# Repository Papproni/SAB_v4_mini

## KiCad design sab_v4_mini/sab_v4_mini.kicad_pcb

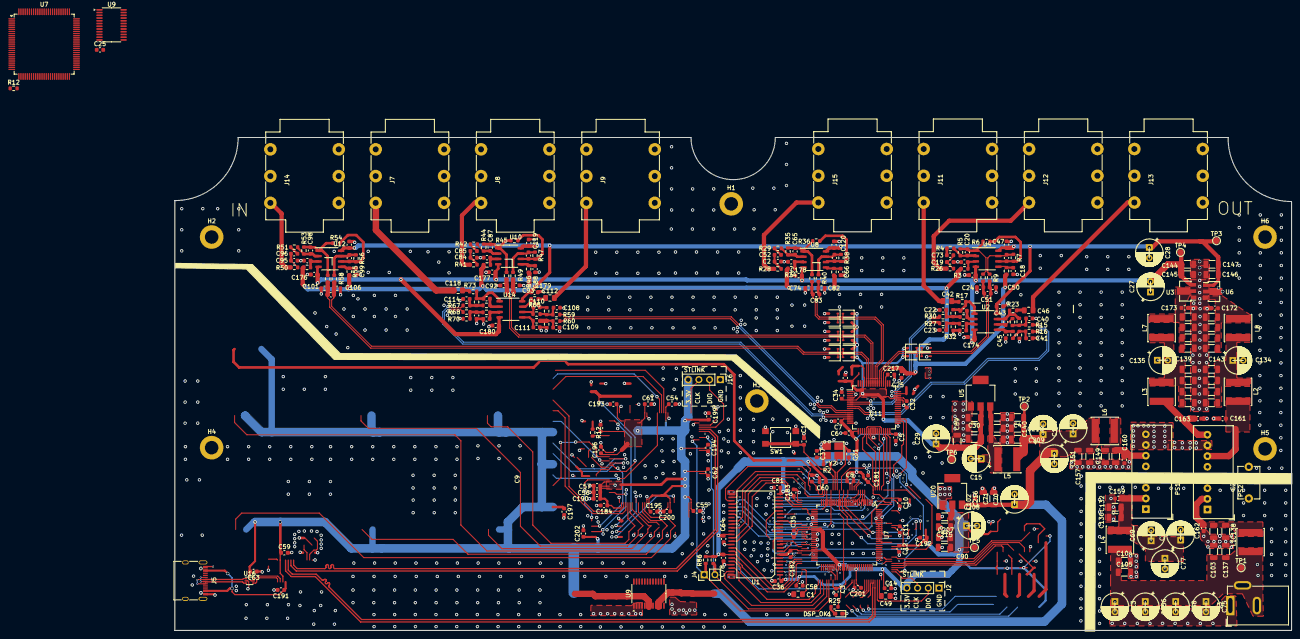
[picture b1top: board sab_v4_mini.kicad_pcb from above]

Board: 4 copper layers, 265.0 x 117.0 mm, 337 parts (0 on the bottom side), 104 nets.

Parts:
C1, C42, C46, C49, C112, C118: 2.2uF; C_0805_2012Metric_Pad1.18x1.45mm_HandSolder
C2, C19, C21, C38, C39, C44, C45, C51, C72, C83, C84, C91, C94, C95, C100, C107, C110, C111, C116, C117: 100pF; C_0603_1608Metric
C3, C5, C6, C7, C8, C9, C10, C11, C12, C14, C16, C17, C18, C25, C25#2, C32, C33, C34, C35, C36, C43, C47, C52, C53, C54, C55, C56, C57, C58, C59, C60, C61, C62, C63, C64, C66, C73, C78, C81, C85, C86, C88, C96, C97, C99, C102, C113, C119, C120, C159, C160, C161, C162, C163, C172, C173, C174, C175, C176, C177, C178, C179, C180, C181, C182, C183, C184, C190, C191, C192, C193, C194, C195, C196, C197, C198, C199, C200, C201, C202, C217: 100nF; C_0603_1608Metric
C4, C30, C71, C89, C90, C103, C104, C105, C132, C133, C136, C137, C138, C139, C141, C142, C143, C144, C145, C146, C147, C148, C149, C152, C153, C154, C155, C157, C158, C164, C165, C166, C167, C168, C169, C170, C171, C205, C206, C207, C209, C210, C211, C212, C213, C214, C215, C216: 10uF; C_1206_3216Metric
C13, C15, C27, C28, C29, C48, C69, C70, C75, C76, C77, C134, C135, C140, C150, C151, C156, C208: 100uF; CP_Radial_D6.3mm_P2.50mm_reference_fix
C20, C65, C87, C98: 1p; C_0603_1608Metric
C22, C23, C40, C41, C108, C109, C114, C115: 470pF; C_0603_1608Metric
C24, C50, C74, C82, C92, C93, C101, C106: 1nF; C_0603_1608Metric
C31, C37: 12pF; C_0603_1608Metric
C229: 1nF; C_Disc_D7.5mm_W5.0mm_P7.50mm
D1, D4, D5, D6, D7, D8, D9, D12, D13, D14, D15, D16, D17, D18, D19, D20: 1N5819; D_SOD-323
DSP_OK1: LED; LED_0603_1608Metric_Pad1.05x0.95mm_HandSolder
H1, H2, H3, H4, H5, H6: MountingHole_Pad; MountingHole_3.2mm_M3_DIN965_Pad
J2: STlink_DSP; PinHeader_1x04_P2.54mm_Vertical
J3: Barrel_Jack_Switch; BarrelJack_GCT_DCJ200-10-A_Horizontal
J4: Conn_01x02_i2c; PinHeader_1x02_P2.54mm_Vertical
J5: USB_C_Receptacle_USB2.0; USB_C_Receptacle_XKB_U262-16XN-4BVC11
J7: AudioJack_LOOP1_SEND; 6.3_jack_new_ref
J8: AudioJack_LOOP1_RETURN; 6.3_jack_new_ref
J9: AudioJack_LOOP2_SEND; 6.3_jack_new_ref
J11: AudioJack_LOOP3_SEND; 6.3_jack_new_ref
J12: AudioJack_LOOP3_RETURN; 6.3_jack_new_ref
J13: AudioJack_OUTPUT; 6.3_jack_new_ref
J14: AudioJack_INPUT; 6.3_jack_new_ref
J15: AudioJack_LOOP2_RETURN; 6.3_jack_new_ref
J16: STlink_DISP_MCU; PinHeader_1x04_P2.54mm_Vertical
L1, L2, L3, L4, L5, L6, L7, L8: 10uH; L_Sunlord_SWPA6020S
PS1: URB2405S-6WR3; Converter_DCDC_XP_POWER-ITxxxxxS_THT
PS2: WRA2412S-3WR2; Converter_DCDC_XP_POWER-ITxxxxxS_THT
R2, R3, R8, R9, R11, R26, R28, R34, R37, R39, R40, R41, R43, R46, R48, R49, R50, R52, R55, R57, R58: 100R; R_0603_1608Metric
R4, R29, R42, R51: 1M; R_0603_1608Metric
R5, R35, R44, R53: 510k; R_0603_1608Metric
R6, R7, R36, R38, R45, R47, R54, R56: 4k7; R_0603_1608Metric
R12, R12#2: 10k; R_0603_1608Metric
R13, R14, R15, R16, R19, R20, R21, R22, R27, R30, R31, R32, R59, R60, R61, R62, R63, R64, R66, R67, R68, R69, R70, R71, R72, R86: 3k; R_0603_1608Metric
R17, R23, R25, R65, R73: 1k; R_0603_1608Metric
SW1: SW_SPST; SW_SPST_TL3305A
TP1: TestPoint_PWR_IN; TestPoint_Pad_D1.5mm
TP2: TestPoint_5V; TestPoint_Pad_D1.5mm
TP3: TestPoint_9V; TestPoint_Pad_D1.5mm
TP4: TestPoint_-9V; TestPoint_Pad_D1.5mm
TP5: TestPoint_3V3; TestPoint_Pad_D1.5mm
TP6: TestPoint_3V3A; TestPoint_Pad_D1.5mm
U1: IS42S16100H-7TL; TSOP-2-50-new
U2, U4, U8, U10, U12, U14: OP275; SSOP-8_3.9x5.05mm_P1.27mm
U3: 7909; SOT-89-3
U5, U20: AP1117-33; SOT-223
U6: 7809; SOT-89-3
U7, U7#2: STM32H750VBTx; LQFP-100_14x14mm_P0.5mm
U9, U9#2: CS4270; TSSOP-24_4.4x7.8mm_P0.65mm
U11: LQFP-64_10x10mm_P0.5mm
U16: USBLC6-2P6; SOT-666
Y2: X1E0000210132; Crystal_SMD_SeikoEpson_TSX3225-4Pin_3.2x2.5mm_HandSoldering

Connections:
5V: C4.1, C70.1, C71.1, C102.1, C140.1, C148.1, C150.1, C151.1, C157.1, C209.1, C210.1, C216.1, L5.1, L6.2, TP2.1, U20.3 (VI)
+3.3V: C3.1, C5.1, C6.1, C7.1, C8.1, C9.1, C10.1, C11.1, C12.1, C14.1, C35.1, C36.1, C54.1, C55.1, C56.1, C57.1, C58.1, C59.1, C60.1, C61.1, C62.1, C63.1, C64.1, C78.1, C81.1, C90.1, C181.1, C182.1, C183.1, C184.1, C190.1, C192.1, C193.1, C194.1, C195.1, C196.1, C197.1, C198.1, C199.1, C200.1, C201.1, C202.1, C207.1, C208.1, C214.1, C215.1, J2.4, J16.4, R66.1, R86.1, TP5.1, U1.1 (VDD), U1.7 (VDDQ), U1.13 (VDDQ), U1.25 (VDD), U1.38 (VDDQ), U1.44 (VDDQ), U7.6 (VBAT), U7.11 (VDD), U7.20 (VREF+), U7.21 (VDDA), U7.27 (VDD), U7.50 (VDD), U7.75 (VDD), U7.100 (VDD), U7#2.6 (VBAT), U7#2.11 (VDD), U7#2.20 (VREF+), U7#2.21 (VDDA), U7#2.27 (VDD), U7#2.50 (VDD), U7#2.75 (VDD), U7#2.100 (VDD), U11.17 (DVDD), U11.32 (DVDD), U16.5 (VBUS), U20.2 (VO)
+3.3VA: C29.1, C30.1, C32.1, C33.1, C34.1, C89.1, C205.1, C206.1, C217.1, D4.1 (K), D5.1 (K), D7.1 (K), D9.1 (K), D13.1 (K), D15.1 (K), D17.1 (K), D19.1 (K), TP6.1, U5.2 (VO), U11.5 (AVDD), U11.45 (AVDD), U11.51 (AVDD), U11.62 (AVDD)
+9V: C28.1, C43.1, C47.1, C113.1, C119.1, C120.1, C146.1, C147.1, C179.1, TP3.1, U2.8 (V+), U4.8 (V+), U6.1 (OUT), U8.8 (V+), U10.8 (V+), U12.8 (V+), U14.8 (V+)
-9V: C27.2, C144.1, C145.1, C174.2, C175.2, C176.2, C177.2, C178.2, C180.2, TP4.1, U2.4 (V-), U3.3 (VO), U4.4 (V-), U8.4 (V-), U10.4 (V-), U12.4 (V-), U14.4 (V-)
/MCU/USB_Conn_D+: J5.A6 (D+), J5.B6 (D+), U16.1 (I/O1)
/MCU/USB_Conn_D-: J5.A7 (D-), J5.B7 (D-), U16.3 (I/O2)
/Power/+12V: C161.1, L2.1, PS2.6 (+Vout)
/Power/-12V: C163.1, L3.1, PS2.8 (-Vout)
ADC1N: C24.2, C51.2, D5.2 (A), D6.1 (K), R8.1
ADC1P: C50.1, C51.1, D1.1 (K), D4.2 (A), R9.1
ADC2N: C74.2, C83.2, D7.2 (A), D8.1 (K), R39.1
ADC2P: C82.1, C83.1, D9.2 (A), D12.1 (K), R40.1
ADC3N: C92.2, C94.2, D17.2 (A), D18.1 (K), R48.1
ADC3P: C93.1, C94.1, D19.2 (A), D20.1 (K), R49.1
ADC4N: C101.2, C107.2, D13.2 (A), D14.1 (K), R57.1
ADC4P: C106.1, C107.1, D15.2 (A), D16.1 (K), R58.1
Audio_Loop1_Return: J8.T, R41.1
Audio_Loop1_Send: C118.2, J7.T
Audio_Loop2_Return: J15.T, R28.1
Audio_Loop2_Send: C112.2, J9.T
Audio_Loop3_Return: C1.2, C2.1, C3.2, C4.2, C5.2, C6.2, C7.2, C8.2, C9.2, C10.2, C11.2, C12.2, C14.2, C15.2, C16.2, C17.2, C18.2, C19.1, C22.1, C23.2, C24.1, C27.1, C28.2, C29.2, C30.2, C31.1, C32.2, C33.2, C34.2, C35.2, C36.2, C37.1, C38.1, C40.1, C41.2, C43.2, C45.1, C47.2, C49.2, C50.2, C53.2, C54.2, C55.2, C56.2, C57.2, C58.2, C59.2, C60.2, C61.2, C62.2, C63.2, C64.2, C66.2, C70.2, C71.2, C74.1, C78.2, C81.2, C82.2, C84.1, C86.2, C88.2, C89.2, C90.2, C92.1, C93.2, C95.1, C97.2, C99.2, C101.1, C102.2, C106.2, C108.1, C109.2, C111.1, C113.2, C114.1, C115.2, C117.1, C119.2, C120.2, C134.2, C135.1, C139.2, C140.2, C141.2, C142.2, C143.2, C144.2, C145.2, C146.2, C147.2, C148.2, C149.2, C150.2, C151.2, C152.2, C153.2, C154.2, C155.2, C157.2, C158.2, C160.2, C161.2, C163.2, C164.2, C165.2, C166.2, C167.2, C168.2, C169.2, C170.2, C171.2, C172.2, C173.2, C174.1, C175.1, C176.1, C177.1, C178.1, C179.2, C180.1, C181.2, C182.2, C183.2, C184.2, C190.2, C191.2, C192.2, C193.2, C194.2, C195.2, C196.2, C197.2, C198.2, C199.2, C200.2, C201.2, C202.2, C205.2, C206.2, C207.2, C208.2, C209.2, C210.2, C211.2, C212.2, C213.2, C214.2, C215.2, C216.2, C217.2, C229.2, D1.2 (A), D6.2 (A), D8.2 (A), D12.2 (A), D14.2 (A), D16.2 (A), D18.2 (A), D20.2 (A), DSP_OK1.1 (K), H1.1, H2.1, H3.1, H4.1, H5.1, H6.1, J2.1, J5.A1 (GND), J5.A12 (GND), J5.B1 (GND), J5.B12 (GND), J8.TN, J12.T, J12.TN, J14.TN, J15.TN, J16.1, PS1.7 (-Vout), PS2.7 (Common), R20.1, R26.1, R32.1, R62.1, R70.1, SW1.2 (B), U1.4 (GNDQ), U1.10 (GNDQ), U1.26 (GND), U1.41 (GNDQ), U1.47 (GNDQ), U1.50 (GND), U3.1 (GND), U5.1 (GND), U6.2 (GND), U7.10 (VSS), U7.19 (VSSA), U7.26 (VSS), U7.49 (VSS), U7.74 (VSS), U7.99 (VSS), U7#2.10 (VSS), U7#2.19 (VSSA), U7#2.26 (VSS), U7#2.49 (VSS), U7#2.74 (VSS), U7#2.99 (VSS), U11.1 (AGND), U11.4 (AGND), U11.16 (DGND), U11.23 (VSUPPLY), U11.24 (VSENSE), U11.25 (VDRIVE), U11.33 (DGND), U11.44 (AGND), U11.46 (AGND), U11.48 (AGND), U16.2 (GND), U20.1 (GND), Y2.2, Y2.4
Audio_Loop3_Send: C42.2, J11.T
Audio_Main_Input: J14.T, R50.1
Audio_Main_Output: C46.2, J13.T
DSP_VBUS: C191.1, J5.A4 (VBUS), J5.A9 (VBUS), J5.B4 (VBUS), J5.B9 (VBUS)
Earth: C13.2, C48.2, C69.2, C75.2, C76.2, C77.2, C103.2, C104.2, C105.2, C132.2, C133.2, C136.2, C137.2, C138.2, C156.2, C159.2, C162.2, C229.1, J3.1, PS1.1 (-Vin), PS2.1 (-Vin)
I2C_SCL: J4.2, R66.2
I2C_SDA: J4.1, R86.2
NRST: C16.1, SW1.1 (A), U7.14 (NRST), U7#2.14 (NRST)
unnamed: C1.1, U7.48 (VCAP), U7#2.48 (VCAP)
unnamed: C2.2, C52.2, R28.2
unnamed: C19.2, C73.2, R26.2
unnamed: C20.2, R5.1, R6.2, R8.2, U4.1
unnamed: C21.2, R7.1, R9.2, U4.7
unnamed: C22.2, R13.1, R30.2, R31.1
unnamed: C23.1, R14.2, R27.2, R32.2
unnamed: C37.2, R2.2, Y2.3
unnamed: C39.2, R17.2, R31.2, U2.1
unnamed: C40.2, R15.2, R19.1, R21.1
unnamed: C41.1, R16.2, R20.2, R22.2
unnamed: C42.1, R17.1
unnamed: C44.2, R19.2, R23.2, U2.7
unnamed: C46.1, R23.1
unnamed: C49.1, U7.73 (VCAP), U7#2.73 (VCAP)
unnamed: C52.1, R29.2
unnamed: C65.2, R35.1, R36.2, R39.2, U8.1
unnamed: C72.2, R38.1, R40.2, U8.7
unnamed: C73.1, R4.2
unnamed: C84.2, C85.2, R41.2
unnamed: C85.1, R42.2
unnamed: C87.2, R44.1, R45.2, R48.2, U10.1
unnamed: C91.2, R47.1, R49.2, U10.7
unnamed: C95.2, C96.2, R50.2
unnamed: C96.1, R51.2
unnamed: C98.2, R53.1, R54.2, R57.2, U12.1
unnamed: C100.2, R56.1, R58.2, U12.7
unnamed: C108.2, R59.2, R61.1, R63.1
unnamed: C109.1, R60.2, R62.2, R64.2
unnamed: C110.2, R61.2, R65.2, U14.7
unnamed: C112.1, R65.1
unnamed: C114.2, R67.2, R69.1, R71.1
unnamed: C115.1, R68.2, R70.2, R72.2
unnamed: C116.2, R69.2, R73.2, U14.1
unnamed: C118.1, R73.1
unnamed: C134.1, C142.1, C143.1, C152.1, C153.1, L2.2, L8.1
unnamed: C135.2, C139.1, C141.1, C154.1, C155.1, L3.2, L7.1
unnamed: DSP_OK1.2 (A), R25.1
unnamed: R12.2, R12#2.2
unnamed: C69.1, C76.1, C77.1, C132.1, C136.1, C159.1, L4.2, PS1.2 (+Vin)
unnamed: C149.1, C158.1, C160.1, L6.1, PS1.6 (+Vout)
unnamed: C133.1, C138.1, C162.1, L1.2, PS2.2 (+Vin)
unnamed: C38.2, R14.1, U2.3 (+)
unnamed: C39.1, R13.2, U2.2 (-)
unnamed: C45.2, R22.1, U2.5 (+)
unnamed: C44.1, R21.2, U2.6 (-)
unnamed: C165.1, C166.1, C167.1, C168.1, C173.1, L7.2, U3.2 (VI)
unnamed: C17.1, R3.1, U4.3 (+)
unnamed: C20.1, R4.1, R5.2, U4.2 (-)
unnamed: C18.1, R11.1, U4.5 (+)
unnamed: C21.1, R6.1, R7.2, U4.6 (-)
unnamed: C15.1, C211.1, C212.1, C213.1, L5.2, U5.3 (VI)
unnamed: C164.1, C169.1, C170.1, C171.1, C172.1, L8.2, U6.3 (IN)
unnamed: C53.1, R34.1, U8.3 (+)
unnamed: C65.1, R29.1, R35.2, U8.2 (-)
unnamed: C66.1, R37.1, U8.5 (+)
unnamed: C72.1, R36.1, R38.2, U8.6 (-)
unnamed: C86.1, R43.1, U10.3 (+)
unnamed: C87.1, R42.1, R44.2, U10.2 (-)
unnamed: C88.1, R46.1, U10.5 (+)
unnamed: C91.1, R45.1, R47.2, U10.6 (-)
unnamed: C97.1, R52.1, U12.3 (+)
unnamed: C98.1, R51.1, R53.2, U12.2 (-)
unnamed: C99.1, R55.1, U12.5 (+)
unnamed: C100.1, R54.1, R56.2, U12.6 (-)
unnamed: C117.2, R72.1, U14.3 (+)
unnamed: C116.1, R71.2, U14.2 (-)
unnamed: C111.2, R64.1, U14.5 (+)
unnamed: C110.1, R63.2, U14.6 (-)
OSC0: C31.2, U7.12 (PH0), U7#2.12 (PH0), Y2.1
OSC1: R2.1, U7.13 (PH1), U7#2.13 (PH1)
PWR_INPUT_12V-18V: C13.1, C48.1, C75.1, C103.1, C104.1, C105.1, C137.1, C156.1, J3.2, J3.3, L1.1, L4.1, TP1.1
VBIAS: R3.2, R11.2, R34.2, R37.2, R43.2, R46.2, R52.2, R55.2
to_BOOT0: R12.1, R12#2.1, U7.94 (BOOT0), U7#2.94 (BOOT0)

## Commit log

2025-03-22 added base project
    copied project files from v3
2025-03-22 deleted unused pin added mcu
    stm32h750vbt6
2025-03-22 added codec
2025-03-22 basic project created in CubeIDE
2025-03-22 basic configurations done
2025-05-31 moved codec
